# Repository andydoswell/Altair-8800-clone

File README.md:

# Altair-8800-clone
# Files to create an Altair 8800 clone based on Arduino Due. 
# Detail on Andydoz.blogspot.com

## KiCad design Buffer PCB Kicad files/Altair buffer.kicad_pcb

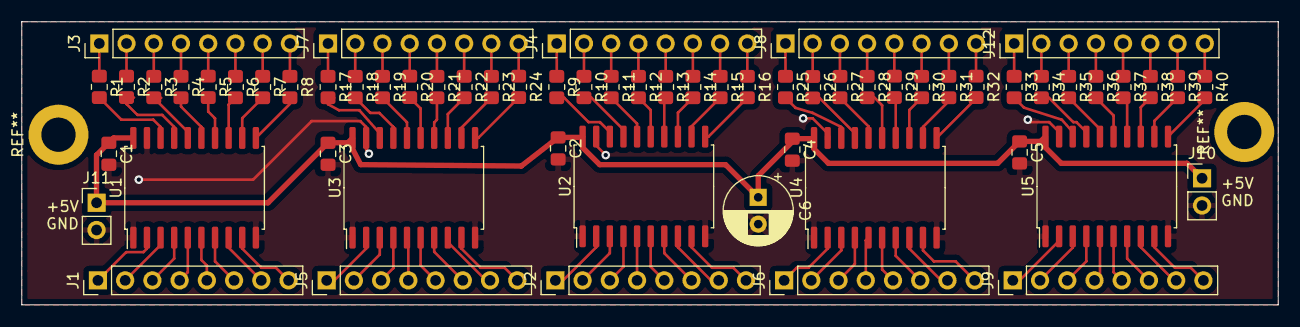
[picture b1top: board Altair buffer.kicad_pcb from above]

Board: 2 copper layers, 117.2 x 26.4 mm, 63 parts (0 on the bottom side), 122 nets.

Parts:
C1, C2, C3, C4, C5: 0.1u; C_0805_2012Metric_Pad1.15x1.40mm_HandSolder
C6: 100u; CP_Radial_D6.3mm_P2.50mm
J1: In Bank 0; PinHeader_1x08_P2.54mm_Vertical
J2: In Bank 2; PinHeader_1x08_P2.54mm_Vertical
J3: LED Bank 0; PinHeader_1x08_P2.54mm_Vertical
J4: LED Bank 2; PinHeader_1x08_P2.54mm_Vertical
J5: In Bank 1; PinHeader_1x08_P2.54mm_Vertical
J6: In Bank 3; PinHeader_1x08_P2.54mm_Vertical
J7: LED Bank 1; PinHeader_1x08_P2.54mm_Vertical
J8: LED Bank 3; PinHeader_1x08_P2.54mm_Vertical
J9: In Bank 4; PinHeader_1x08_P2.54mm_Vertical
J10, J11: PWR; PinHeader_1x02_P2.54mm_Vertical
J12: LED Bank 4; PinHeader_1x08_P2.54mm_Vertical
R1, R2, R3, R4, R5, R6, R7, R8, R9, R10, R11, R12, R13, R14, R15, R16, R17, R18, R19, R20, R21, R22, R23, R24, R25, R26, R27, R28, R29, R30, R31, R32, R33, R34, R35, R36, R37, R38, R39, R40: 470; R_0805_2012Metric_Pad1.20x1.40mm_HandSolder
U1, U2, U3, U4, U5: 74HCT541; SOIC-20W_7.5x12.8mm_P1.27mm

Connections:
+5V: C1.1, C2.1, C3.1, C4.1, C5.1, C6.1, J10.1, J11.1, U1.20, U2.20, U3.20, U4.20, U5.20
GND: C1.2, C2.2, C3.2, C4.2, C5.2, C6.2, J10.2, J11.2, U1.1, U1.10, U1.19, U2.1, U2.10, U2.19, U3.1, U3.10, U3.19, U4.1, U4.10, U4.19, U5.1, U5.10, U5.19
unnamed: J1.1, U1.2
unnamed: J1.2, U1.3
unnamed: J1.3, U1.4
unnamed: J1.4, U1.5
unnamed: J1.5, U1.6
unnamed: J1.6, U1.7
unnamed: J1.7, U1.8
unnamed: J1.8, U1.9
unnamed: J2.1, U2.2
unnamed: J2.2, U2.3
unnamed: J2.3, U2.4
unnamed: J2.4, U2.5
unnamed: J2.5, U2.6
unnamed: J2.6, U2.7
unnamed: J2.7, U2.8
unnamed: J2.8, U2.9
unnamed: J3.1, R1.1
unnamed: J3.2, R2.1
unnamed: J3.3, R3.1
unnamed: J3.4, R4.1
unnamed: J3.5, R5.1
unnamed: J3.6, R6.1
unnamed: J3.7, R7.1
unnamed: J3.8, R8.1
unnamed: J4.1, R9.1
unnamed: J4.2, R10.1
unnamed: J4.3, R11.1
unnamed: J4.4, R12.1
unnamed: J4.5, R13.1
unnamed: J4.6, R14.1
unnamed: J4.7, R15.1
unnamed: J4.8, R16.1
unnamed: J5.1, U3.2
unnamed: J5.2, U3.3
unnamed: J5.3, U3.4
unnamed: J5.4, U3.5
unnamed: J5.5, U3.6
unnamed: J5.6, U3.7
unnamed: J5.7, U3.8
unnamed: J5.8, U3.9
unnamed: J6.1, U4.2
unnamed: J6.2, U4.3
unnamed: J6.3, U4.4
unnamed: J6.4, U4.5
unnamed: J6.5, U4.6
unnamed: J6.6, U4.7
unnamed: J6.7, U4.8
unnamed: J6.8, U4.9
unnamed: J7.1, R17.1
unnamed: J7.2, R18.1
unnamed: J7.3, R19.1
unnamed: J7.4, R20.1
unnamed: J7.5, R21.1
unnamed: J7.6, R22.1
unnamed: J7.7, R23.1
unnamed: J7.8, R24.1
unnamed: J8.1, R25.1
unnamed: J8.2, R26.1
unnamed: J8.3, R27.1
unnamed: J8.4, R28.1
unnamed: J8.5, R29.1
unnamed: J8.6, R30.1
unnamed: J8.7, R31.1
unnamed: J8.8, R32.1
unnamed: J9.1, U5.2
unnamed: J9.2, U5.3
unnamed: J9.3, U5.4
unnamed: J9.4, U5.5
unnamed: J9.5, U5.6
unnamed: J9.6, U5.7
unnamed: J9.7, U5.8
unnamed: J9.8, U5.9
unnamed: J12.1, R33.1
unnamed: J12.2, R34.1
unnamed: J12.3, R35.1
unnamed: J12.4, R36.1
unnamed: J12.5, R37.1
unnamed: J12.6, R38.1
unnamed: J12.7, R39.1
unnamed: J12.8, R40.1
unnamed: R1.2, U1.18
unnamed: R2.2, U1.17
unnamed: R3.2, U1.16
unnamed: R4.2, U1.15
unnamed: R5.2, U1.14
unnamed: R6.2, U1.13
unnamed: R7.2, U1.12
unnamed: R8.2, U1.11
unnamed: R9.2, U2.18
unnamed: R10.2, U2.17
unnamed: R11.2, U2.16
unnamed: R12.2, U2.15
unnamed: R13.2, U2.14
unnamed: R14.2, U2.13
unnamed: R15.2, U2.12
unnamed: R16.2, U2.11
unnamed: R17.2, U3.18
unnamed: R18.2, U3.17
unnamed: R19.2, U3.16
unnamed: R20.2, U3.15
unnamed: R21.2, U3.14
unnamed: R22.2, U3.13
unnamed: R23.2, U3.12
unnamed: R24.2, U3.11
unnamed: R25.2, U4.18
unnamed: R26.2, U4.17
unnamed: R27.2, U4.16
unnamed: R28.2, U4.15
unnamed: R29.2, U4.14
unnamed: R30.2, U4.13
unnamed: R31.2, U4.12
unnamed: R32.2, U4.11
unnamed: R33.2, U5.18
unnamed: R34.2, U5.17
unnamed: R35.2, U5.16
unnamed: R36.2, U5.15
unnamed: R37.2, U5.14
unnamed: R38.2, U5.13
unnamed: R39.2, U5.12
unnamed: R40.2, U5.11
